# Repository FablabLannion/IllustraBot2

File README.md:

IllustraBot2
============

This is a [Fablab Lannion](http://fablab-lannion.org) project.
Purpose is to control a robotic arm over 4G using movments from an android phone.

You can find more info on the [wiki](http://fablab-lannion.org/wiki/index.php?title=IllustraBot2)

List of directories :
* DOC : documentation (datasheets, ...)
* Kicad : electronic scheme
* android : well, android application
* beaglebone : soft running on the arm control platform

test

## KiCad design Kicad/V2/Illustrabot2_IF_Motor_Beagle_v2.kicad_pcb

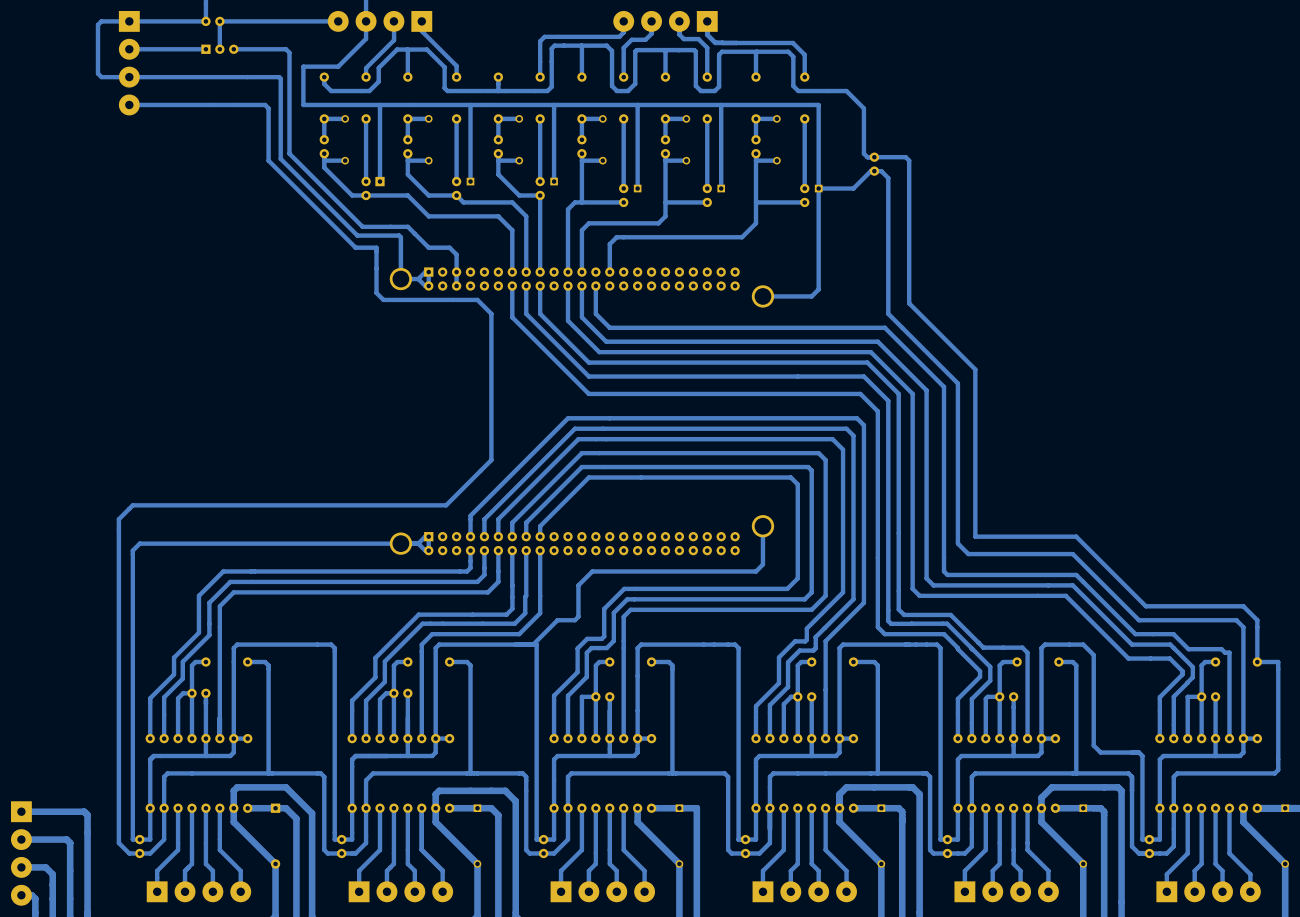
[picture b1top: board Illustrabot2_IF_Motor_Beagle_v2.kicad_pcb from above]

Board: 2 copper layers, 79 parts (0 on the bottom side), 81 nets.

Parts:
C1, C2, C7, C8, C11, C12: 100uF; CP4
C3, C4, C15, C16, C17, C18, C19, C20: 10uF; C1
C5, C6, C9, C10, C13, C14: 100nF; C1
D1, D2, D3, D4, D5, D6: LED; LED-3MM
JP1: JUMPER3; SIL-3
P1, P2, P3, P4, P5, P6, P7, P10, P11, P12: CONN_4; bornier4
P8, P9: CONN_23X2; SIL-2x23-v1
P13, P14, P15, P16: CONN_1; 1pin
Q1, Q2, Q3, Q4, Q5, Q6: NPN; TO92
R1, R2, R3, R4, R10, R12: 10kohm; R3
R5, R7, R9, R13, R15, R17: 150ohm; R3
R6, R8, R11, R14, R16, R18: 82kohm; R3
R19, R20, R21, R22, R23, R24: 47k; R3
U1, U2, U3, U4, U5, U6: STEPSTICK; Stepstick_footprint

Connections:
3V3: C3.1, C15.2, C16.2, C17.2, C18.2, C19.2, C20.2, P3.4, R1.2, R2.2, R3.2, R4.2, R5.1, R7.1, R9.1, R10.2, R12.2, R13.1, R15.1, R17.1, U1.10, U2.10, U3.10, U4.10, U5.10, U6.10
+5V: C4.2, JP1.2, P11.4
+12C: C2.1, C7.1, C11.1, P4.4, U2.16, U3.16, U5.16
+12V: C1.1, C8.1, C12.1, P4.2, U1.16, U4.16, U6.16
/1A_M1: P1.2, U1.12
/1A_M2: P12.2, U6.12
/1A_M3: P6.2, U4.12
/1A_M4: P2.2, U2.12
/1A_M5: P5.2, U3.12
/1A_M6: P7.2, U5.12
/1B_M1: P1.1, U1.11
/1B_M2: P12.1, U6.11
/1B_M3: P6.1, U4.11
/1B_M4: P2.1, U2.11
/1B_M5: P5.1, U3.11
/1B_M6: P7.1, U5.11
/2A_M1: P1.3, U1.13
/2A_M2: P12.3, U6.13
/2A_M3: P6.3, U4.13
/2A_M4: P2.3, U2.13
/2A_M5: P5.3, U3.13
/2A_M6: P7.3, U5.13
/2B_M1: P1.4, U1.14
/2B_M2: P12.4, U6.14
/2B_M3: P6.4, U4.14
/2B_M4: P2.4, U2.14
/2B_M5: P5.4, U3.14
/2B_M6: P7.4, U5.14
/Beaglebone_5V: JP1.3, P9.5, P9.6
/Direction_m2: P8.14, U6.8
/Direction_m3: P8.17, U4.8
/Direction_m4: P8.11, U2.8
/Direction_m5: P9.14, U3.8
/Direction_m6: P9.22, U5.8
/External 5V: JP1.1, P3.2
/Position_m1: D1.2, P9.13, Q1.3, R19.2
/Position_m2: D2.2, P9.15, Q2.3, R20.2
/Position_m3: D3.2, P9.17, Q3.3, R21.2
/Position_m4: D4.2, P9.21, Q4.3, R22.2
/Position_m5: D5.2, P9.23, Q5.3, R23.2
/Position_m6: D6.2, P9.27, Q6.3, R24.2
/Step_m1: P8.10, U1.7
/Step_m2: P8.16, U6.7
/Step_m3: P8.15, U4.7
/Step_m4: P8.9, U2.7
/Step_m5: P9.16, U3.7
/Step_m6: P9.24, U5.7
/direction_m1: P8.8, U1.8
/ms2_m1: P8.12, U1.3
/ms2_m2: P8.18, U6.3
/ms2_m3: P8.13, U4.3
/ms2_m4: P8.7, U2.3
/ms2_m5: P9.18, U3.3
/ms2_m6: P9.26, U5.3
AGND: C1.2, C8.2, C12.2, P4.1, U1.15, U4.15, U6.15
GND: C3.2, C4.1, C5.2, C6.2, C9.2, C10.2, C13.2, C14.2, C15.1, C16.1, C17.1, C18.1, C19.1, C20.1, P3.1, P3.3, P8.1, P8.2, P9.1, P9.2, P11.3, P13.1, P14.1, P15.1, P16.1, Q1.1, Q2.1, Q3.1, Q4.1, Q5.1, Q6.1, U1.1, U1.2, U1.4, U1.9, U2.1, U2.2, U2.4, U2.9, U3.1, U3.2, U3.4, U3.9, U4.1, U4.2, U4.4, U4.9, U5.1, U5.2, U5.4, U5.9, U6.1, U6.2, U6.4, U6.9
GNDA: C2.2, C7.2, C11.2, P4.3, U2.15, U3.15, U5.15
unnamed: C5.1, R1.1, U1.5, U1.6
unnamed: C14.1, R12.1, U6.5, U6.6
unnamed: C6.1, R2.1, U2.5, U2.6
unnamed: C13.1, R10.1, U5.5, U5.6
unnamed: C9.1, R3.1, U3.5, U3.6
unnamed: C10.1, R4.1, U4.5, U4.6
unnamed: P11.1, R8.2
unnamed: D1.1, R5.2, R19.1
unnamed: Q3.2, R11.1
unnamed: P10.4, R11.2
unnamed: D2.1, R7.2, R20.1
unnamed: Q2.2, R8.1
unnamed: D3.1, R9.2, R21.1
unnamed: Q1.2, R6.1
unnamed: Q4.2, R14.1
unnamed: D4.1, R13.2, R22.1
unnamed: Q5.2, R16.1
unnamed: D5.1, R15.2, R23.1
unnamed: Q6.2, R18.1
unnamed: D6.1, R17.2, R24.1
unnamed: P10.2, R16.2
unnamed: P10.3, R14.2
unnamed: P10.1, R18.2
unnamed: P11.2, R6.2

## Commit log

2014-01-09 document carte detection bras
2014-01-10 Init repository
2014-01-10 illustration fonctionnement bras
2014-01-14 ncurses TUI for motor test program
2014-01-14 nicer tui
2014-01-14 small bug on boundaries
2014-01-14 Add 0-9 keys
2014-01-14 schéma carte détection
2014-01-14 export schema_carte_detection to pdf
2014-01-15 Change gpio pin
2014-01-15 Add Device Tree Overlay
2014-01-15 bash script to test motors
2014-01-15 First motor_test executable
2014-01-15 A bit more advanced motor tests
2014-01-18 export pdf
2014-01-19 1st dialog protocol version
2014-01-19 Add motor control
2014-01-19 Better joystick management
2014-01-20 move libmsock to local file
2014-01-20 thread implementation for motor control
2014-01-20 Prepare for multiples motors
2014-01-20 Add a second motor
2014-01-21 int/ptr cast warnings cleanup
2014-01-21 Increase (a bit) SimpleGPIO performances
2014-01-21 Compilation correction (msock)
2014-01-21 Create model documentation
2014-01-21 bug in message_t model
2014-01-27 Add some test functions
2014-01-28 Add 1st python client for test
2014-01-30 doc a4988
2014-01-30 Update I/F Beaglebone / Bras robotisé
2014-01-30 Ajout doc stepstick + transistor
2014-02-03 Update : - Missing resistor value - pins on beaglebone to define - double motor supply
2014-02-06 Code documentation
2014-02-06 Code documentation (bis)
2014-02-06 schema implementation
2014-02-08 Footprint association Component placing
2014-02-11 schema implantation
2014-02-11 Routing
2014-02-14 Final routing
2014-02-28 Add android messages
2014-02-28 define android message type
2014-03-01 set gpios for 6 motors
2014-03-01 Add MS2 gestion for easydriver
2014-03-01 TODO's update
2014-03-02 DTS for motors (not compiled/tested)
2014-03-04 Add joystick/android control for all 6 motors (some code from damiensh22)
2014-03-05 Remove b5 for android
2014-03-05 Test branche
2014-03-06 Set duration for stepstick drivers states
2014-03-06 * tcp thread added for nonblocking mode * sensors retrieve, thanks HTML5 :-) * send binaryframe with a period defined in ib2_tools.js
    Use Case:
    - press "starttraffic" to start sending frame to tcp socket
    - press "stopptraffic" to ... stop traffic
    - Debug modes:
    opensocket : open tcp connection
    sendpattern: send a hardcoded raw frame
2014-03-07 Update new ranges for android
2014-03-08 test git damien
2014-03-08 test de la branche damien 2e
2014-03-08 ajout ed_poll gpio_fd_open_g, modif gpio_export gpio_unexport gpio_set_edge ed_init ed_step
2014-03-11 Update dts/gpios for end detections
2014-03-11 Get motor end position
2014-03-13 update joystick axis / commanded motor
2014-03-13 Move motor6 detection to P9_27
    P9_25 already reserved for mcasp0_pins
2014-03-13 trap socket close wire connection status to plugin api
2014-03-13 update for android
2014-03-13 add close API for tcp plugin update frontend to change IP, port and sample period update frontend to select motor to be controlled
2014-03-15 Modification P9 header (pin 25 -> pin 27)
2014-05-21 Add compiled dtbo for beaglebone
2014-05-26 Ajout d'une résistance de 47kohm en parallèle led
2014-09-03 Add slider bar and toggle. TODO : connect front end to tcp frame, button 1&2
2014-09-23 rework android app to use ionic framework and angularjs power :-)
2014-09-23 Poster
2014-09-23 Added new app under git
2014-09-24 update template
2014-09-26 cleanup README.txt file
2014-09-26 - front end updated for Galaxy S2 - arm/hand buttons added
    see README.txt for TODO list
2014-09-26 align release number to 0.4
2014-09-28 0.0.5 release: - frontend updated, back to portait mode to ease galaxy S2 keyboard usage - slider not working fine on galaxy S2 : fixed ( width to be improved) - load/save not working fine on galaxy 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
2014-10-01 missing png file
2014-10-01 update front end for dashboard select arm by default ignore local.properties files to ease portability
2014-10-01 bugfix with cross-laptops platform structure. Note : android directory should be git ignored, should be feasible once res/drawable will be batched....
2014-10-02 update default values for VM IP
2014-10-03 bugfix with parameters load/save connect fronend timer to backend timer.
2014-10-13 release 0.0.8 used for innovation campus
